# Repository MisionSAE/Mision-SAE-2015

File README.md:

# Mision-SAE-2015

En este repositorio se presenta y deja a disposición de los interesados material generado en la edición 2015 del Proyecto Misión SAE. En el mismo se podrá encontrar el firmware y hardware desarrollados para el vuelo del prototipo del dispositivo SAE, así como plantillas y ejemplos de trabajo para la programación de los dispositivos.

<h2>Estructura del repositorio</h2>

* **Prototipo SAE:** Código fuente y diseño de hardware utilizados en la construcción del prototipo del dispositivo SAE.

	* **_Firmware:_** Código fuente del firmware del prototipo SAE y ejemplos de desarrollo.

		* _PrototipoSAE:_ Firmware utilizado en los lanzamientos de validación del prototipo SAE
		
			* PropositoGeneral: Firmware de propósito general del prototipo SAE, conformado por la versión 0.6.1 del firmware del Proyecto CIAA (https://github.com/ciaa/Firmware)

			* PropositoEspecifico: Código fuente de las aplicaciones necesarias para llevar adelante la misión primaría de la Misión SAE. Contiene biblioteca para el uso del transmisor XBee, la memoria externa y los sensores de presión, aceleración y temperatura.

		* _MaterialdeTrabajo:_ Plantilla y ejemplos de desarrollo brindados a los participantes de la edición 2015 del proyecto Misión SAE.

	* **_Hardware:_** Bibliotecas, esquemáticos y PCB para el diseño de la placa de integración o poncho que se utilizó como interfaz entre la placa EDU-CIAA y los componentes del Kit SAE. Para su diseño se utilizó la versión (2013-07-07 BZR 4022)-stable de KiCad.

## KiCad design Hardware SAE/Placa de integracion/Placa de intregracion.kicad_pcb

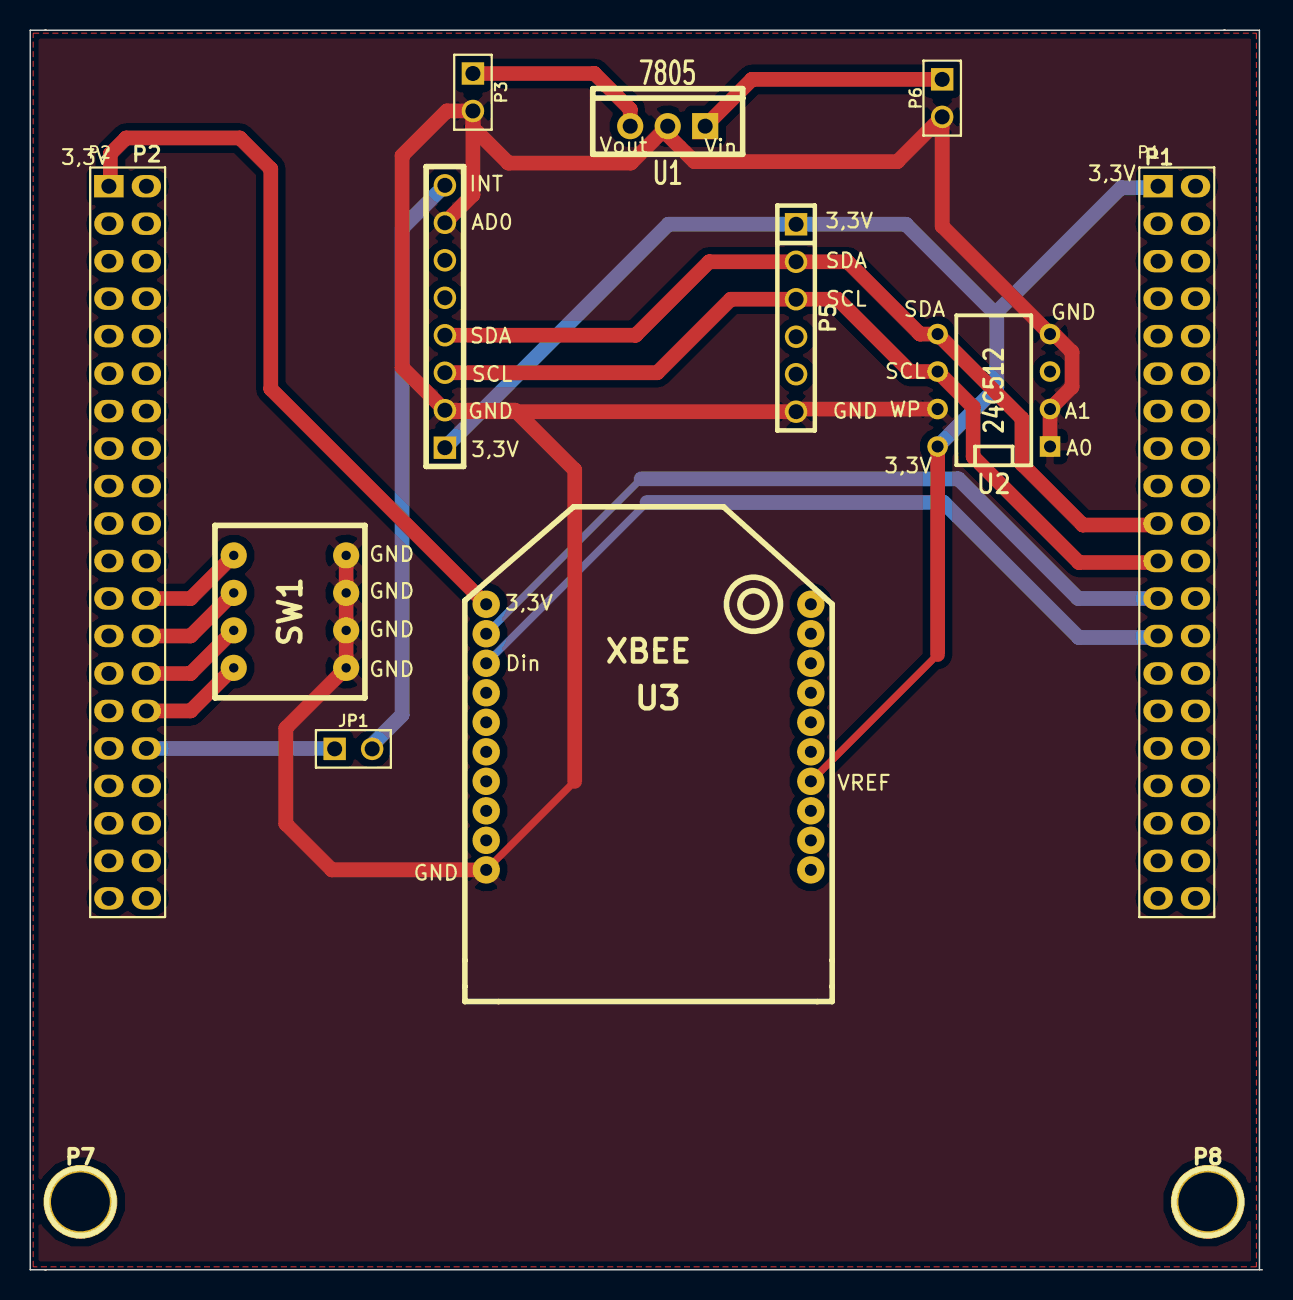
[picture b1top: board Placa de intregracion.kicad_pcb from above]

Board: 2 copper layers, 83.5 x 84.0 mm, 13 parts (0 on the bottom side), 14 nets.

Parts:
JP1: JUMPER; PIN_ARRAY_2X1
P1: P1; PIN_ARRAY_20X2
P2: P2; PIN_ARRAY_20X2
P3: Vout; PIN_ARRAY_2X1
P4: MPU6050; pin_array_8x1
P5: BMP085; PIN_ARRAY-6X1
P6: Vin; PIN_ARRAY_2X1
P7, P8: CONN_1; 1pin
SW1: DIPS_04; DIPS-DS04
U1: 7805; TO220_VERT
U2: 24C512; DIP-8__300
U3: XBEE; XBee-pro

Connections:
+3.3V: P1.1, P2.1, P4.1, P5.1, U2.8, U3.1, U3.14
GND: P3.2, P4.2, P4.7, P5.6, P6.2, SW1.1, SW1.2, SW1.3, SW1.4, U1.3, U2.1, U2.2, U2.4, U2.7, U3.10
unnamed: JP1.1, P2.32
unnamed: JP1.2, P4.8
unnamed: P1.25, U3.3
unnamed: P6.1, U1.1
unnamed: P2.30, SW1.8
unnamed: P2.28, SW1.7
unnamed: P2.26, SW1.6
unnamed: P2.24, SW1.5
unnamed: P1.23, U3.2
unnamed: P3.1, U1.2
unnamed: P1.19, P4.4, P5.2, U2.5
unnamed: P1.21, P4.3, P5.3, U2.6

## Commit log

2016-02-26 Upload
